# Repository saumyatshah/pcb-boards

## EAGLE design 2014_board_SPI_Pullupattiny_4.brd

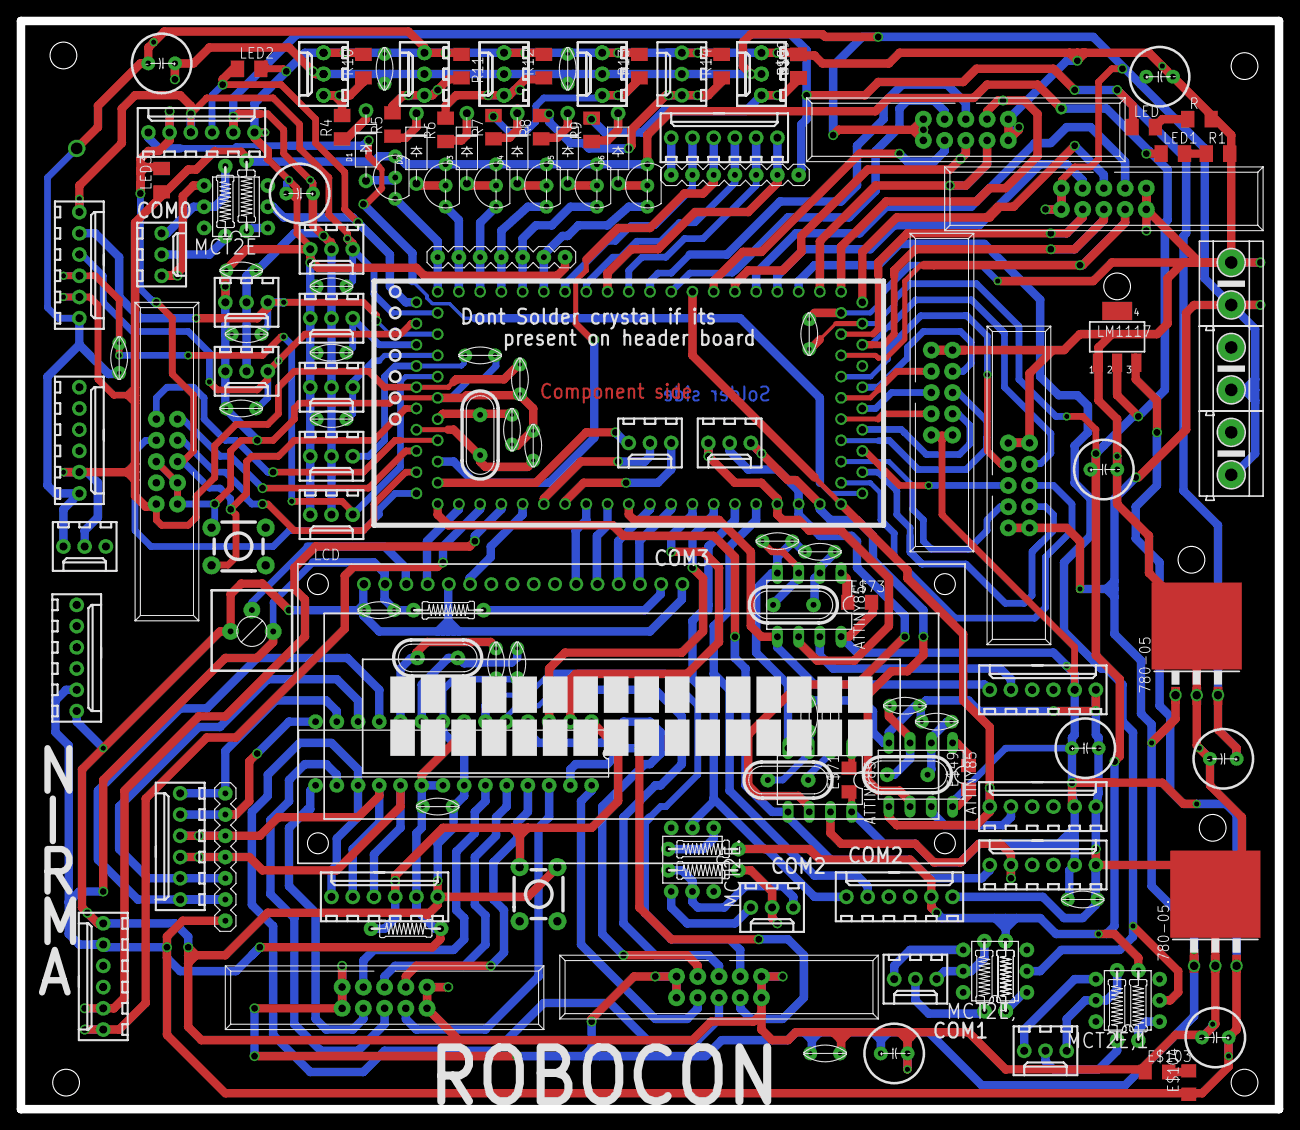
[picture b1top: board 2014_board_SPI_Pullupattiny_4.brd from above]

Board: 2 copper layers, 150.5 x 130.2 mm, 152 parts (0 on the bottom side), 96 nets.

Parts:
780-05, 780-05.: TO263-3
ATTINY85, ATTINY85,, ATTINY85.: DIL08
D1, D2, D3, D4, D5, D6: DIODE(1N4007)
E$1: LPC1769-HEADER
E$2, E$18, E$27, E$30, E$40: CRYSTAL
E$3, E$4, E$5, E$6, E$15, E$19, E$20, E$25, E$26, E$28, E$29, E$31, E$39, E$42, E$43, E$51, E$57, E$61, E$62, E$66, E$67, E$85, E$86, E$97, E$98, E$145: CAPACITOR(CERAMIC)
E$7, E$8, E$46, E$47, E$56, E$64, E$65: FRC(10)
E$9, E$12, E$14, E$16, E$17, E$33, E$35, E$48, E$50, E$52, E$53, E$54, E$55, E$58, E$59, E$60, E$68, E$76, E$89, E$91, E$92, E$93, E$94, E$96, E$102: CONNECTOR(3_PIN)
E$10, E$21, E$22, E$23, E$32, E$37, E$44, E$83, E$84, E$87, E$88, E$106: CONNECTOR(6_PIN)
E$11, E$72, E$113: RESISTER_ARRAY(7)
E$13, E$34, E$36, E$45, E$69, E$70, E$74, E$75, E$95, E$100, E$101: RESISTER(HORIZONTAL)
E$24, E$90, E$118, E$119, E$120, E$121, E$141, E$144: CAPACITOR(ELECTROLYTE_220)
E$38: POT(SQAURE)
E$41: ATMEGA8
E$49, E$71, E$73: R1206
E$63, E$107: SWITCH(PUSH-BUTTON)
E$77, E$78, E$79, E$80, E$81, E$82: TRANSISTOR(TO92-HALF_ROUND)
E$99: M1206
E$103, E$104: C1206
E$108, E$109, E$110: CONNECTOR(GREEN)
LCD: TUXGR_16X2_R2
LED, LED1, LED2, LED3: M1206
LM1117: SOT223
MCT2E, MCT2E,, MCT2E,1, MCT2E.: DIL6
R, R1, R4, R5, R6, R7, R8, R9, R10, R11, R12, R13, R14, R15: M1206

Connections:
3.3V: E$1.P$15, E$1.P$77, E$32.2, E$56.5, E$77.C, E$78.C, E$79.C, E$80.C, E$81.C, E$82.C, E$83.2, E$87.2, E$89.2
5V_PERIPHERALS: ATTINY85.8, ATTINY85,.8, ATTINY85..8, E$8.1, E$8.10, E$11.1, E$21.2, E$22.2, E$23.2, E$37.2, E$41.AREF, E$41.AVCC, E$41.VCC, E$44.2, E$88.2
5V_SHARP: E$50.2, E$52.2, E$53.2, E$54.2, E$55.2, E$58.2, E$59.2, E$84.2, E$113.7
12V: E$7.10, E$46.1, E$46.10, E$47.1, E$47.10, E$65.1, E$65.10, E$91.2, E$92.P$2, E$93.P$2, E$94.P$2, E$96.P$2, E$108.P$2, E$109.P$2, E$110.P$2
GND: ATTINY85.4, ATTINY85,.4, ATTINY85..4, E$1.P$1, E$1.P$40, E$8.5, E$8.6, E$21.1, E$22.1, E$23.1, E$32.1, E$37.1, E$41.AGND, E$41.GND, E$44.1, E$46.5, E$46.6, E$47.5, E$47.6, E$50.1, E$52.1, E$53.1, E$54.1, E$55.1, E$56.3, E$56.6, E$56.7, E$58.1, E$59.1, E$64.5, E$64.6, E$65.5, E$65.6, E$72.7, E$83.1, E$84.1, E$87.1, E$88.1, E$89.1, E$91.1, E$92.P$1, E$93.P$1, E$94.P$1, E$96.P$1, E$108.P$1
S$1: E$10.6, E$11.2, E$41.PD5
S$2: ATTINY85..7, E$23.5
S$6: E$1.P$44, E$8.7
S$8: ATTINY85,.6, E$1.P$52, E$9.1
S$9: E$1.P$36, E$64.9
S$10: E$1.P$74, E$8.4
S$13: E$1.P$48, E$7.3
S$14: E$10.3, E$11.5, E$41.PB4, E$44.5
S$16: E$10.4, E$11.4, E$41.PB5, E$44.4
S$17: E$1.P$47, E$7.9
S$19: E$1.P$73, E$8.8
S$21: E$1.P$42, E$64.4
S$22: E$1.P$45, E$8.9
S$24: E$1.P$71, E$7.8
S$25: E$1.P$41, E$64.2
S$33: E$7.5, E$7.6
S$34: ATTINY85.5, E$1.P$32, E$1.P$49, E$22.6
S$41: E$76.3, MCT2E,.P$2
S$44: E$1.P$5, E$55.3, E$83.6, E$84.4
S$45: E$1.P$55, E$41.PD1
S$48: ATTINY85.7, E$22.5
S$49: E$41.PC4, E$46.4
S$51: ATTINY85,.7, E$21.5
S$52: ATTINY85..6, E$1.P$51, E$9.2
S$53: ATTINY85..5, E$1.P$68, E$23.6
S$54: ATTINY85.6, E$1.P$50, E$9.3
S$55: E$1.P$66, E$37.6
S$57: E$1.P$53, E$32.5
S$60: E$1.P$20, E$72.1, E$77.E
S$62: ATTINY85,.5, E$1.P$59, E$21.6
S$64: E$64.1, E$64.10
S$65: E$1.P$9, E$48.1
S$67: E$102.1, MCT2E,1.P$3
S$68: E$1.P$27, E$106.3, E$113.4
S$69: E$102.3, MCT2E,1.P$2
S$71: E$35.1, MCT2E..P$3
S$75: E$1.P$11, E$56.2
S$76: E$1.P$29, E$106.2, E$113.5
S$78: E$41.PD4, E$46.7
S$81: E$41.PC5, E$46.2
S$83: E$1.P$62, E$48.3
S$85: E$41.PB3, E$44.6, E$46.3
S$86: E$1.P$63, E$48.2
S$87: E$41.PD3, E$46.8
S$88: E$1.P$4, E$58.3, E$83.5
S$90: E$1.P$56, E$41.PD0
S$91: E$1.P$34, E$65.3
S$93: E$41.PC6, E$44.3
S$94: E$41.PC2, E$47.7
S$95: E$41.PC0, E$47.9
S$96: E$41.PB2, E$47.3
S$97: E$41.PC3, E$47.4
S$98: E$41.PB1, E$47.2
S$99: E$41.PD2, E$46.9
S$100: E$1.P$54, E$32.6, MCT2E..P$5
S$101: E$10.2, E$11.6, E$41.PB0
S$103: E$10.1, E$11.7, E$41.PD7
S$104: E$11.3, E$41.PD6
S$105: E$1.P$2, E$50.3, E$83.3
S$107: E$1.P$65, E$37.5
S$110: E$1.P$18, E$59.3, E$83.4
S$112: E$1.P$21, E$72.2, E$78.E
S$113: E$1.P$16, E$52.3
S$116: E$60.1, MCT2E.P$3
S$118: E$1.P$7, E$56.1
S$121: E$1.P$12, E$56.10
S$122: E$1.P$10, E$56.9
S$123: E$1.P$17, E$54.3
S$124: E$1.P$3, E$53.3
S$126: E$60.3, MCT2E.P$2
S$128: E$1.P$23, E$72.4, E$80.E
S$129: E$1.P$22, E$72.3, E$79.E
S$130: E$1.P$19, E$84.3, MCT2E.P$5
S$134: E$76.1, MCT2E,.P$3
S$135: E$1.P$37, MCT2E,.P$5, MCT2E,1.P$5
S$140: E$1.P$14, E$56.8, E$84.5
S$142: E$1.P$24, E$72.5, E$81.E
S$143: E$1.P$25, E$82.E
S$161: E$1.P$76, E$64.3
S$163: E$1.P$39, E$65.7
S$164: E$1.P$38, E$65.4
S$165: E$1.P$33, E$65.2
S$166: E$1.P$35, E$64.7
S$167: E$41.PC1, E$47.8
S$168: E$1.P$31, E$65.9
S$169: E$1.P$30, E$65.8
S$171: E$1.P$8, E$106.4, E$113.3
S$177: E$1.P$69, E$84.6
S$179: E$1.P$26, E$106.5, E$113.2
S$181: E$1.P$28, E$106.1, E$113.6
S$185: E$106.6, E$113.1
